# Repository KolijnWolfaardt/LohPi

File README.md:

# LohPi
A Lora Hat for Raspberry Pi

The PCB uses a [Semtech SX1301](http://www.semtech.com/images/datasheet/sx1301.pdf) to implement a full gateway for a LoRaWan connection. It is intended to plug into a Raspberri Pi 3 which manages the packet forwarding. 

# RF Frontend
The RF frontend is responsible for mixing down the signal, sampling it as IQ samples, and sending it to the SX1301 IC. For this two [SX1257](http://www.semtech.com/images/datasheet/sx1257.pdf) ICs are used. The schematic of the RF frontend is adapted from [Microchip's Documentation](http://ww1.microchip.com/downloads/en/DeviceDoc/40001827A.pdf).

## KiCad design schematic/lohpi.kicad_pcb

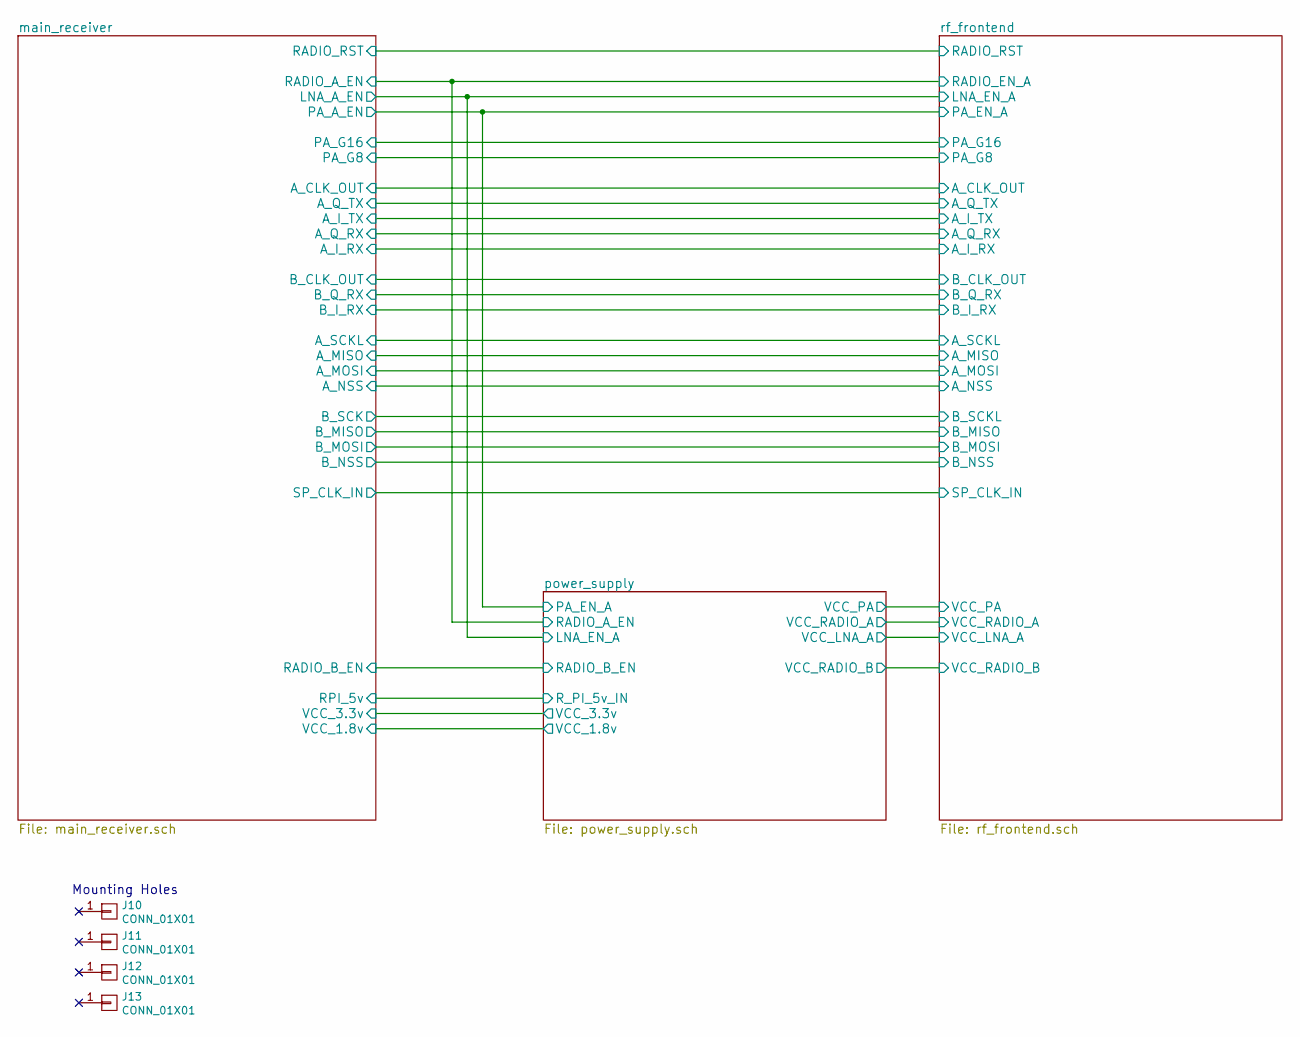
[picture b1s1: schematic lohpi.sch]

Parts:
J10, J11, J12, J13: CONN_01X01; rpi_mounting_hole

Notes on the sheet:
Mounting Holes

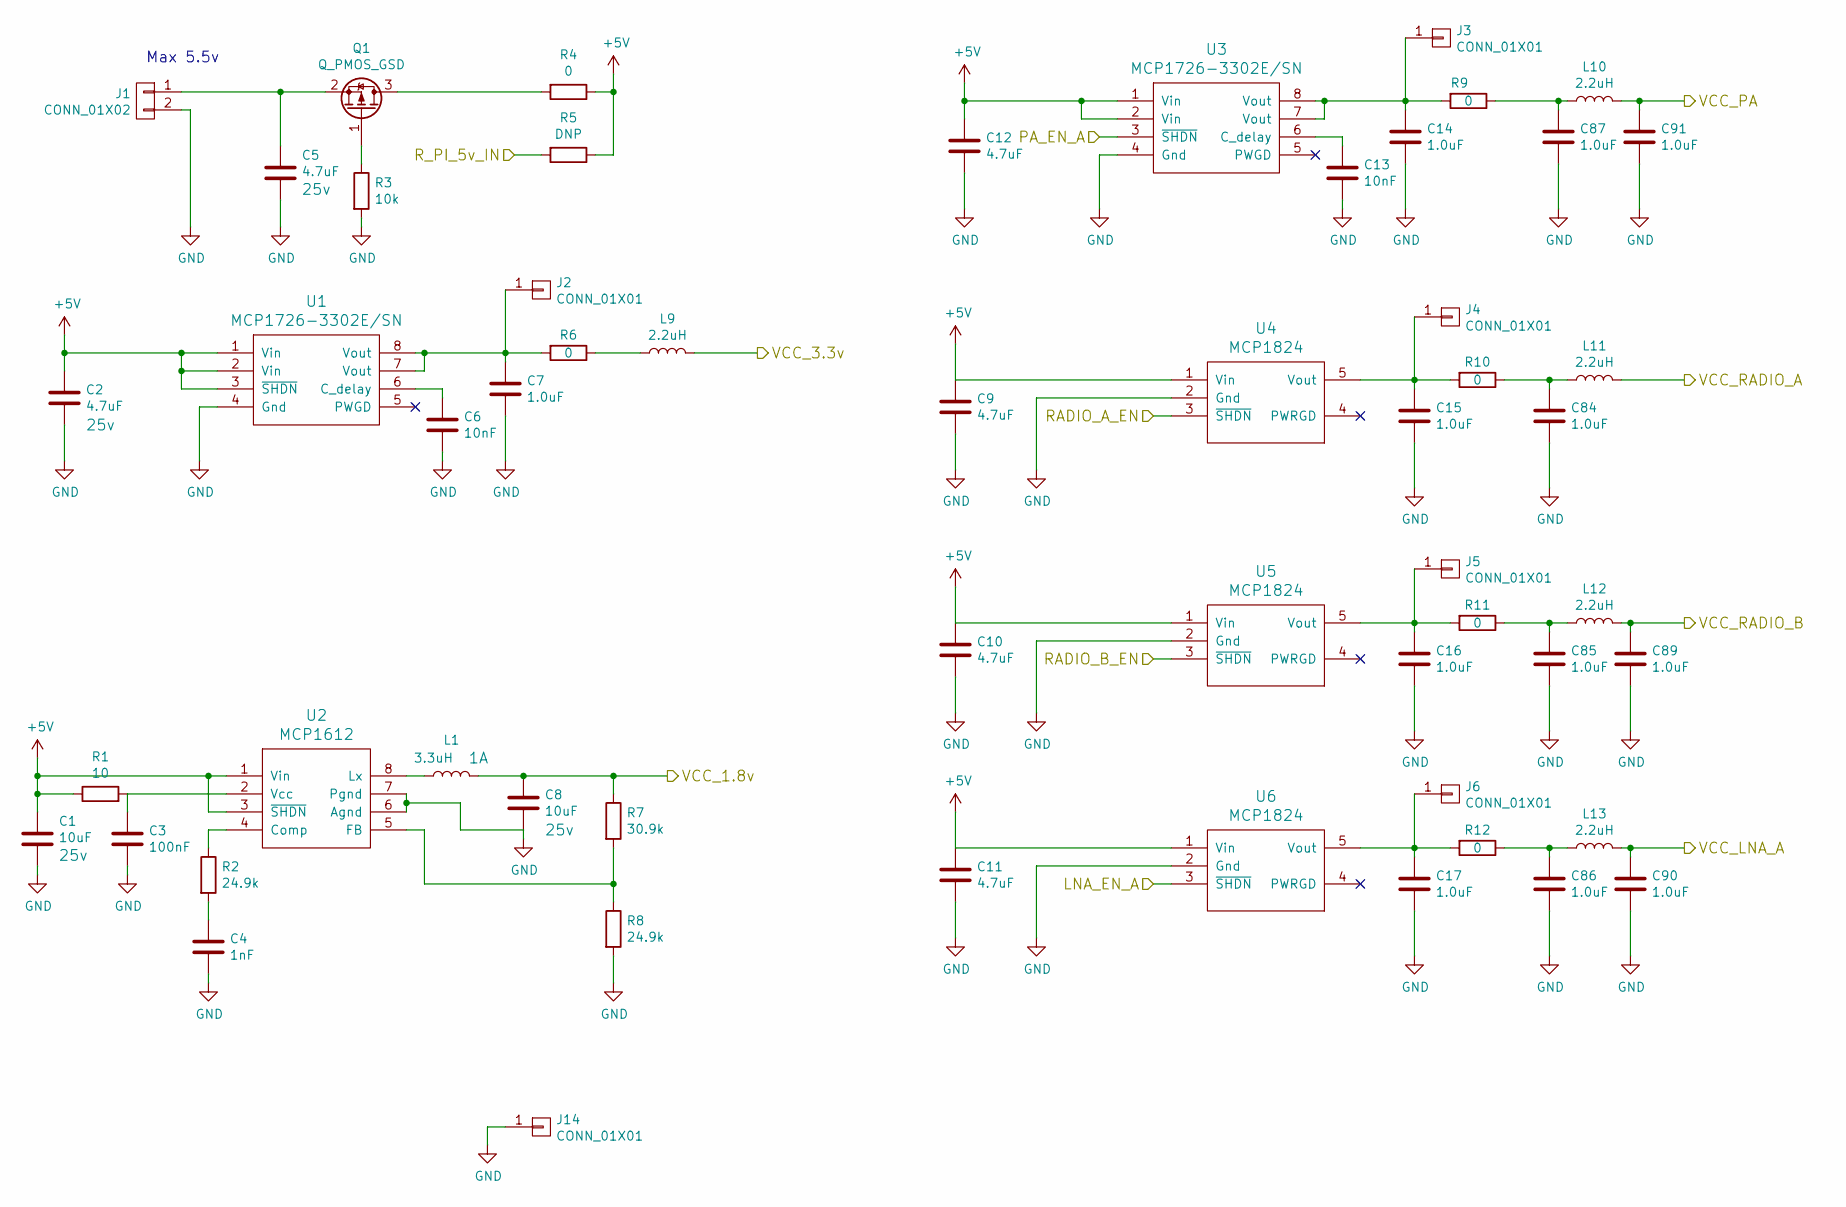
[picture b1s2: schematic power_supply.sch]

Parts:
C1, C8: 10uF; C_0603; Voltage 25v
C2, C5: 4.7uF; C_0603; Voltage 25v
C3: 100nF; C_0603
C4: 1nF; C_0603
C6, C13: 10nF; C_0402_NoSilk
C7, C14, C15, C16, C17, C84, C85, C86, C87, C89, C90, C91: 1.0uF; C_0603
C9, C10, C11, C12: 4.7uF; C_0603
J1: CONN_01X02; Pin_Header_Straight_1x02_Pitch2.54mm
J2, J3, J4, J5, J6, J14: CONN_01X01; Pin_Header_Straight_1x01_Pitch2.54mm
L1: 3.3uH; 84332C
L9, L10, L11, L12, L13: 2.2uH; L_0805
Q1: Q_PMOS_GSD; SOT-23
R1: 10; R_0402_NoSilk
R2, R8: 24.9k; R_0603
R3: 10k; R_0603
R4, R6, R9, R10, R11, R12: 0; R_0603
R5: DNP; R_0603
R7: 30.9k; R_0603
U1, U3: MCP1726-3302E/SN; SOIC-8_3.9x4.9mm_Pitch1.27mm
U2: MCP1612; MSOP-8_3x3mm_Pitch0.65mm
U4, U5, U6: MCP1824; SOT-23-5

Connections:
+1V8: C8.1, L1.2, R7.1; also elsewhere on the board
+3V3: L9.2; also elsewhere on the board
+5V: C1.1, C2.1, C9.1, C10.1, C11.1, C12.1, R1.1, R4.1, R5.1, U1.1 (Vin), U1.2 (Vin), U1.3 (~SHDN), U2.1 (Vin), U2.3 (~SHDN), U3.1 (Vin), U3.2 (Vin), U4.1 (Vin), U5.1 (Vin), U6.1 (Vin)
/main_receiver/LNA_A_EN: U6.3 (~SHDN); also elsewhere on the board
/main_receiver/PA_A_EN: U3.3 (~SHDN); also elsewhere on the board
/main_receiver/RADIO_A_EN: U4.3 (~SHDN); also elsewhere on the board
/main_receiver/RADIO_B_EN: U5.3 (~SHDN); also elsewhere on the board
/main_receiver/RPI_5v: R5.2; also elsewhere on the board
/power_supply/VCC_LNA_A: C90.1, L13.2; also elsewhere on the board
/power_supply/VCC_PA: C91.1, L10.2; also elsewhere on the board
/power_supply/VCC_RADIO_A: L11.2; also elsewhere on the board
/power_supply/VCC_RADIO_B: C89.1, L12.2; also elsewhere on the board
GND: C1.2, C2.2, C3.2, C4.2, C5.2, C6.2, C7.2, C8.2, C9.2, C10.2, C11.2, C12.2, C13.2, C14.2, C15.2, C16.2, C17.2, C84.2, C85.2, C86.2, C87.2, C89.2, C90.2, C91.2, J1.2, J14.1, R3.2, R8.2, U1.4 (Gnd), U2.6 (Agnd), U2.7 (Pgnd), U3.4 (Gnd), U4.2 (Gnd), U5.2 (Gnd), U6.2 (Gnd); also elsewhere on the board
unnamed: C3.1, R1.2, U2.2 (Vcc)
unnamed: C4.1, R2.2
unnamed: C5.1, J1.1, Q1.2 (S)
unnamed: C6.1, U1.6 (C_delay)
unnamed: C7.1, J2.1, R6.2, U1.7 (Vout), U1.8 (Vout)
unnamed: C13.1, U3.6 (C_delay)
unnamed: C14.1, J3.1, R9.2, U3.7 (Vout), U3.8 (Vout)
unnamed: C15.1, J4.1, R10.2, U4.5 (Vout)
unnamed: C16.1, J5.1, R11.2, U5.5 (Vout)
unnamed: C17.1, J6.1, R12.2, U6.5 (Vout)
unnamed: C84.1, L11.1, R10.1
unnamed: C85.1, L12.1, R11.1
unnamed: C86.1, L13.1, R12.1
unnamed: C87.1, L10.1, R9.1
unnamed: L1.1, U2.8 (Lx)
unnamed: L9.1, R6.1
unnamed: Q1.1 (G), R3.1
unnamed: Q1.3 (D), R4.2
unnamed: R2.1, U2.4 (Comp)
unnamed: R7.2, R8.1, U2.5 (FB)

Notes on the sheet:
Max 5.5v

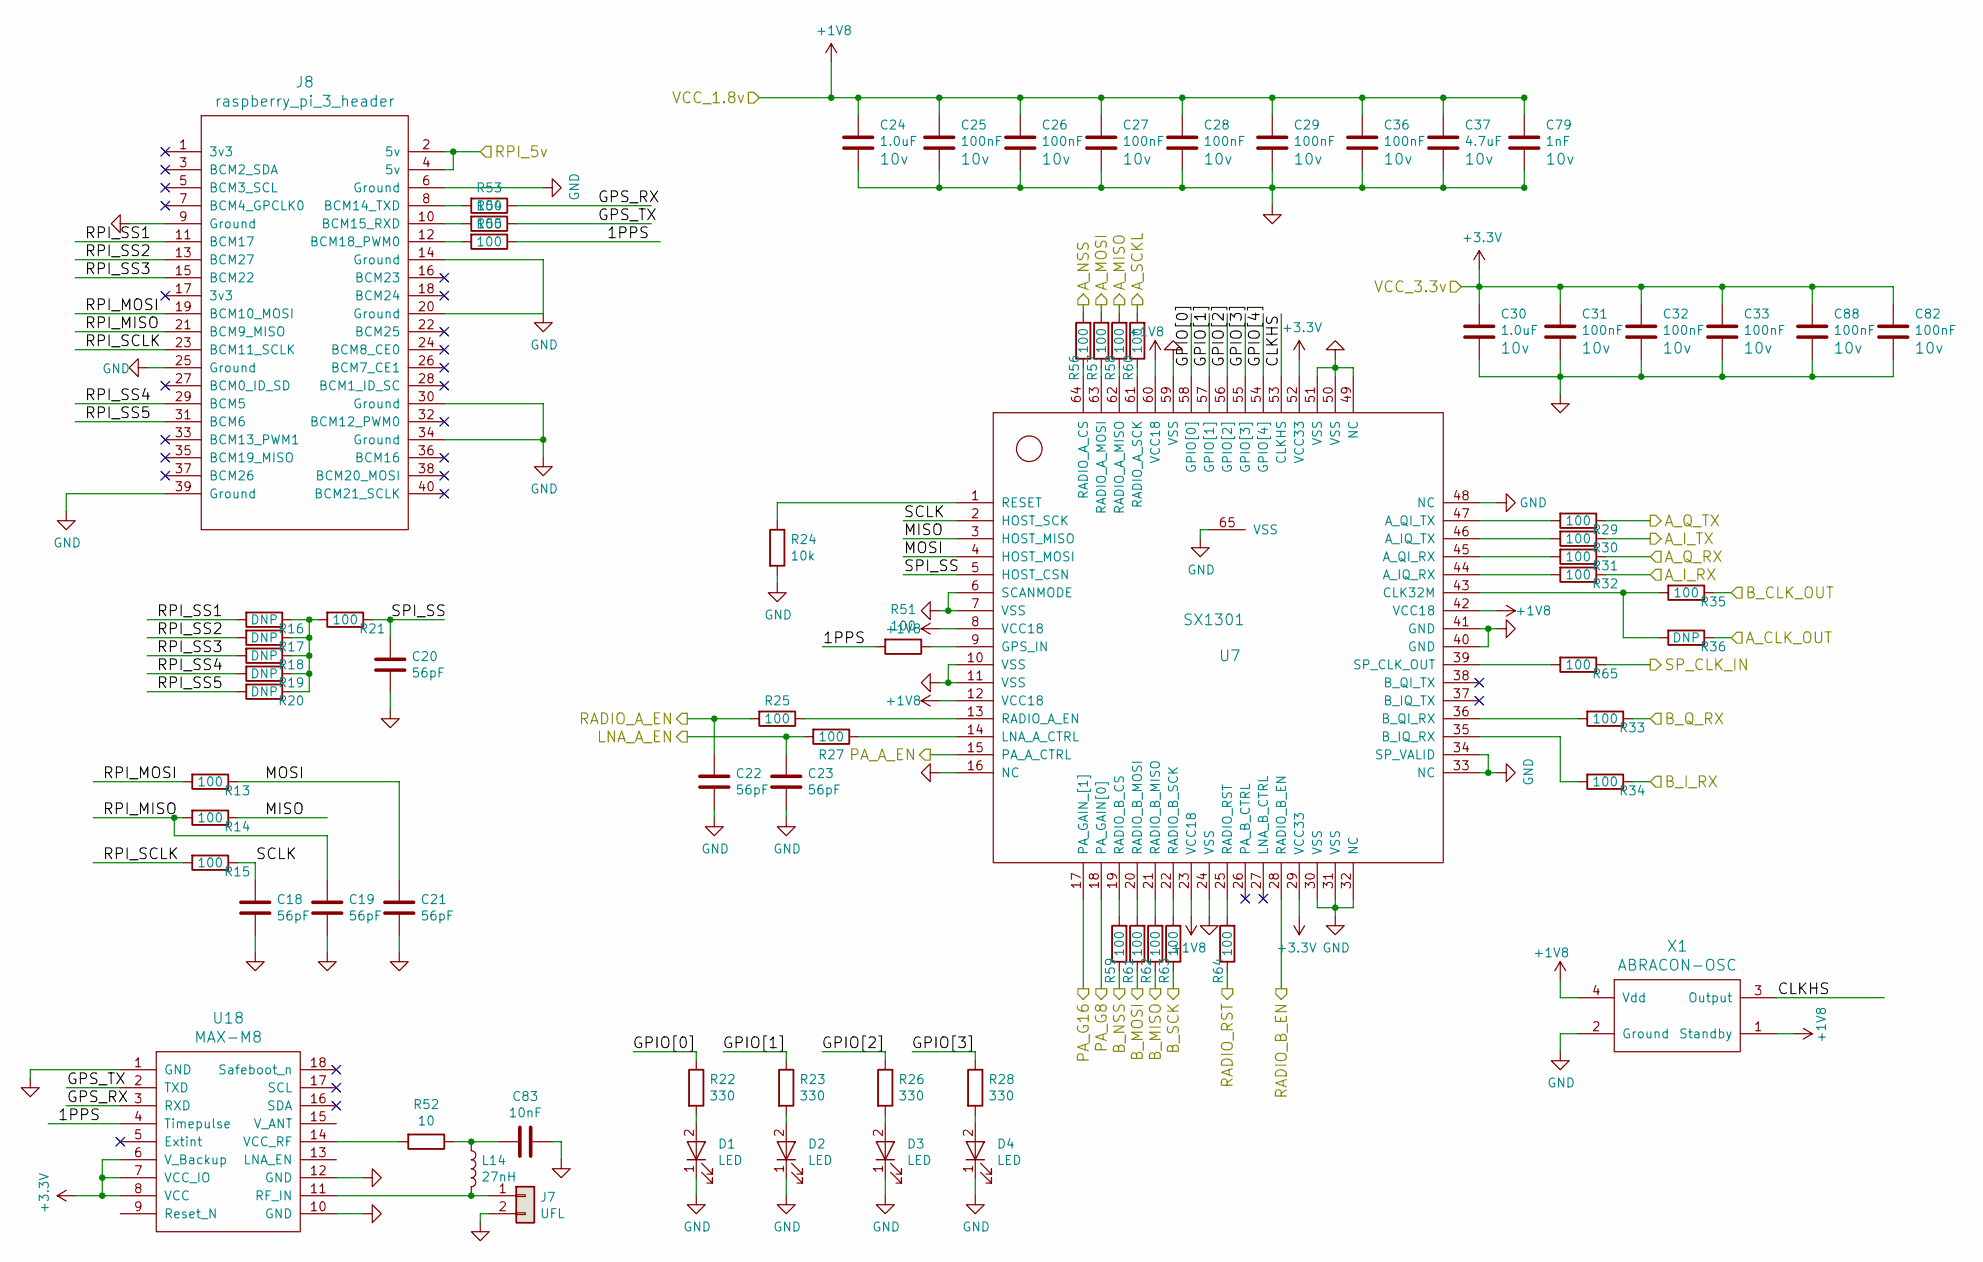
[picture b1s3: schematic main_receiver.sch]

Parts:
C18, C19, C20, C21, C22, C23: 56pF; C_0402_NoSilk
C24, C30: 1.0uF; C_0603; Voltage 10v
C25, C26, C27, C28, C29, C31, C32, C33: 100nF; C_0603; Voltage 10v
C36, C82, C88: 100nF; C_0402_NoSilk; Voltage 10v
C37: 4.7uF; C_0603; Voltage 10v
C79: 1nF; C_0603; Voltage 10v
C83: 10nF; C_0402_NoSilk
D1, D2, D3, D4: LED; LED_0603
J7: UFL; u.fl
J8: raspberry_pi_3_header; Socket_Strip_Straight_2x20_Pitch2.54mm
L14: 27nH; L_0402
R13, R14, R15, R21, R25, R27, R29, R30, R31, R32, R33, R34, R35, R51, R53, R54, R55: 100; R_0603
R16, R17, R18, R19, R20, R36: DNP; R_0603
R22, R23, R26, R28: 330; R_0603
R24: 10k; R_0603
R52: 10; R_0402_NoSilk
R56, R57, R58, R59, R60, R61, R62, R63, R64, R65: 100; R_0402_NoSilk
U7: SX1301; QFN-64-1EP_9x9mm_Pitch0.5mm
U18: MAX-M8
X1: ABRACON-OSC

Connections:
+1V8: C24.1, C25.1, C26.1, C27.1, C28.1, C29.1, C36.1, C37.1, C79.1, U7.8 (VCC18), U7.12 (VCC18), U7.23 (VCC18), U7.42 (VCC18), U7.60 (VCC18), X1.1 (Standby), X1.4 (Vdd); also elsewhere on the board
+3V3: C30.1, C31.1, C32.1, C33.1, C82.1, C88.1, U7.29 (VCC33), U7.52 (VCC33), U18.6 (V_Backup), U18.7 (VCC_IO), U18.8 (VCC); also elsewhere on the board
/main_receiver/1PPS: R51.2, R55.1, U18.4 (Timepulse)
/main_receiver/A_CLK_OUT: R36.1; also elsewhere on the board
/main_receiver/A_I_RX: R32.1; also elsewhere on the board
/main_receiver/A_I_TX: R30.1; also elsewhere on the board
/main_receiver/A_MISO: R58.2; also elsewhere on the board
/main_receiver/A_MOSI: R57.2; also elsewhere on the board
/main_receiver/A_NSS: R56.2; also elsewhere on the board
/main_receiver/A_Q_RX: R31.1; also elsewhere on the board
/main_receiver/A_Q_TX: R29.1; also elsewhere on the board
/main_receiver/A_SCKL: R60.2; also elsewhere on the board
/main_receiver/B_CLK_OUT: R35.1; also elsewhere on the board
/main_receiver/B_I_RX: R34.1; also elsewhere on the board
/main_receiver/B_MISO: R62.1; also elsewhere on the board
/main_receiver/B_MOSI: R61.1; also elsewhere on the board
/main_receiver/B_NSS: R59.1; also elsewhere on the board
/main_receiver/B_Q_RX: R33.1; also elsewhere on the board
/main_receiver/B_SCK: R63.1; also elsewhere on the board
/main_receiver/CLKHS: U7.53 (CLKHS), X1.3 (Output)
/main_receiver/GPIO[0]: R22.1, U7.58 (GPIO[0])
/main_receiver/GPIO[1]: R23.1, U7.57 (GPIO[1])
/main_receiver/GPIO[2]: R26.1, U7.56 (GPIO[2])
/main_receiver/GPIO[3]: R28.1, U7.55 (GPIO[3])
/main_receiver/GPS_RX: R53.1, U18.3 (RXD)
/main_receiver/GPS_TX: R54.1, U18.2 (TXD)
/main_receiver/LNA_A_EN: C23.1, R27.2; also elsewhere on the board
/main_receiver/MISO: R14.1, U7.3 (HOST_MISO)
/main_receiver/MOSI: C21.1, R13.1, U7.4 (HOST_MOSI)
/main_receiver/PA_A_EN: U7.15 (PA_A_CTRL); also elsewhere on the board
/main_receiver/PA_G8: U7.18 (PA_GAIN[0]); also elsewhere on the board
/main_receiver/PA_G16: U7.17 (PA_GAIN_[1]); also elsewhere on the board
/main_receiver/RADIO_A_EN: C22.1, R25.2; also elsewhere on the board
/main_receiver/RADIO_B_EN: U7.28 (RADIO_B_EN); also elsewhere on the board
/main_receiver/RADIO_RST: R64.1; also elsewhere on the board
/main_receiver/RPI_5v: J8.2 (5v), J8.4 (5v); also elsewhere on the board
/main_receiver/RPI_MISO: C19.1, J8.21 (BCM9_MISO), R14.2
/main_receiver/RPI_MOSI: J8.19 (BCM10_MOSI), R13.2
/main_receiver/RPI_SCLK: J8.23 (BCM11_SCLK), R15.2
/main_receiver/RPI_SS1: J8.11 (BCM17), R16.2
/main_receiver/RPI_SS2: J8.13 (BCM27), R17.2
/main_receiver/RPI_SS3: J8.15 (BCM22), R18.2
/main_receiver/RPI_SS4: J8.29 (BCM5), R19.2
/main_receiver/RPI_SS5: J8.31 (BCM6), R20.2
/main_receiver/SCLK: C18.1, R15.1, U7.2 (HOST_SCK)
/main_receiver/SPI_SS: C20.1, R21.1, U7.5 (HOST_CSN)
/main_receiver/SP_CLK_IN: R65.1; also elsewhere on the board
GND: C18.2, C19.2, C20.2, C21.2, C22.2, C23.2, C24.2, C25.2, C26.2, C27.2, C28.2, C29.2, C30.2, C31.2, C32.2, C33.2, C36.2, C37.2, C79.2, C82.2, C83.1, C88.2, D1.1 (K), D2.1 (K), D3.1 (K), D4.1 (K), J7.2, J8.6 (Ground), J8.9 (Ground), J8.14 (Ground), J8.20 (Ground), J8.25 (Ground), J8.30 (Ground), J8.34 (Ground), J8.39 (Ground), R24.2, U7.6 (SCANMODE), U7.7 (VSS), U7.10 (VSS), U7.11 (VSS), U7.16 (NC), U7.24 (VSS), U7.30 (VSS), U7.31 (VSS), U7.32 (NC), U7.33 (NC), U7.34 (SP_VALID), U7.40 (GND), U7.41 (GND), U7.48 (NC), U7.49 (NC), U7.50 (VSS), U7.51 (VSS), U7.59 (VSS), U7.65 (VSS), U18.1 (GND), U18.10 (GND), U18.12 (GND), X1.2 (Ground); also elsewhere on the board
unnamed: C83.2, L14.1, R52.1
unnamed: D1.2 (A), R22.2
unnamed: D2.2 (A), R23.2
unnamed: D3.2 (A), R26.2
unnamed: D4.2 (A), R28.2
unnamed: J7.1, L14.2, U18.11 (RF_IN)
unnamed: J8.8 (BCM14_TXD), R53.2
unnamed: J8.10 (BCM15_RXD), R54.2
unnamed: J8.12 (BCM18_PWM0), R55.2
unnamed: R16.1, R17.1, R18.1, R19.1, R20.1, R21.2
unnamed: R24.1, U7.1 (RESET)
unnamed: R25.1, U7.13 (RADIO_A_EN)
unnamed: R27.1, U7.14 (LNA_A_CTRL)
unnamed: R29.2, U7.47 (A_QI_TX)
unnamed: R30.2, U7.46 (A_IQ_TX)
unnamed: R31.2, U7.45 (A_QI_RX)
unnamed: R32.2, U7.44 (A_IQ_RX)
unnamed: R33.2, U7.36 (B_QI_RX)
unnamed: R34.2, U7.35 (B_IQ_RX)
unnamed: R35.2, R36.2, U7.43 (CLK32M)
unnamed: R51.1, U7.9 (GPS_IN)
unnamed: R52.2, U18.14 (VCC_RF)
unnamed: R56.1, U7.64 (RADIO_A_CS)
unnamed: R57.1, U7.63 (RADIO_A_MOSI)
unnamed: R58.1, U7.62 (RADIO_A_MISO)
unnamed: R59.2, U7.19 (RADIO_B_CS)
unnamed: R60.1, U7.61 (RADIO_A_SCK)
unnamed: R61.2, U7.20 (RADIO_B_MOSI)
unnamed: R62.2, U7.21 (RADIO_B_MISO)
unnamed: R63.2, U7.22 (RADIO_B_SCK)
unnamed: R64.2, U7.25 (RADIO_RST)
unnamed: R65.2, U7.39 (SP_CLK_OUT)

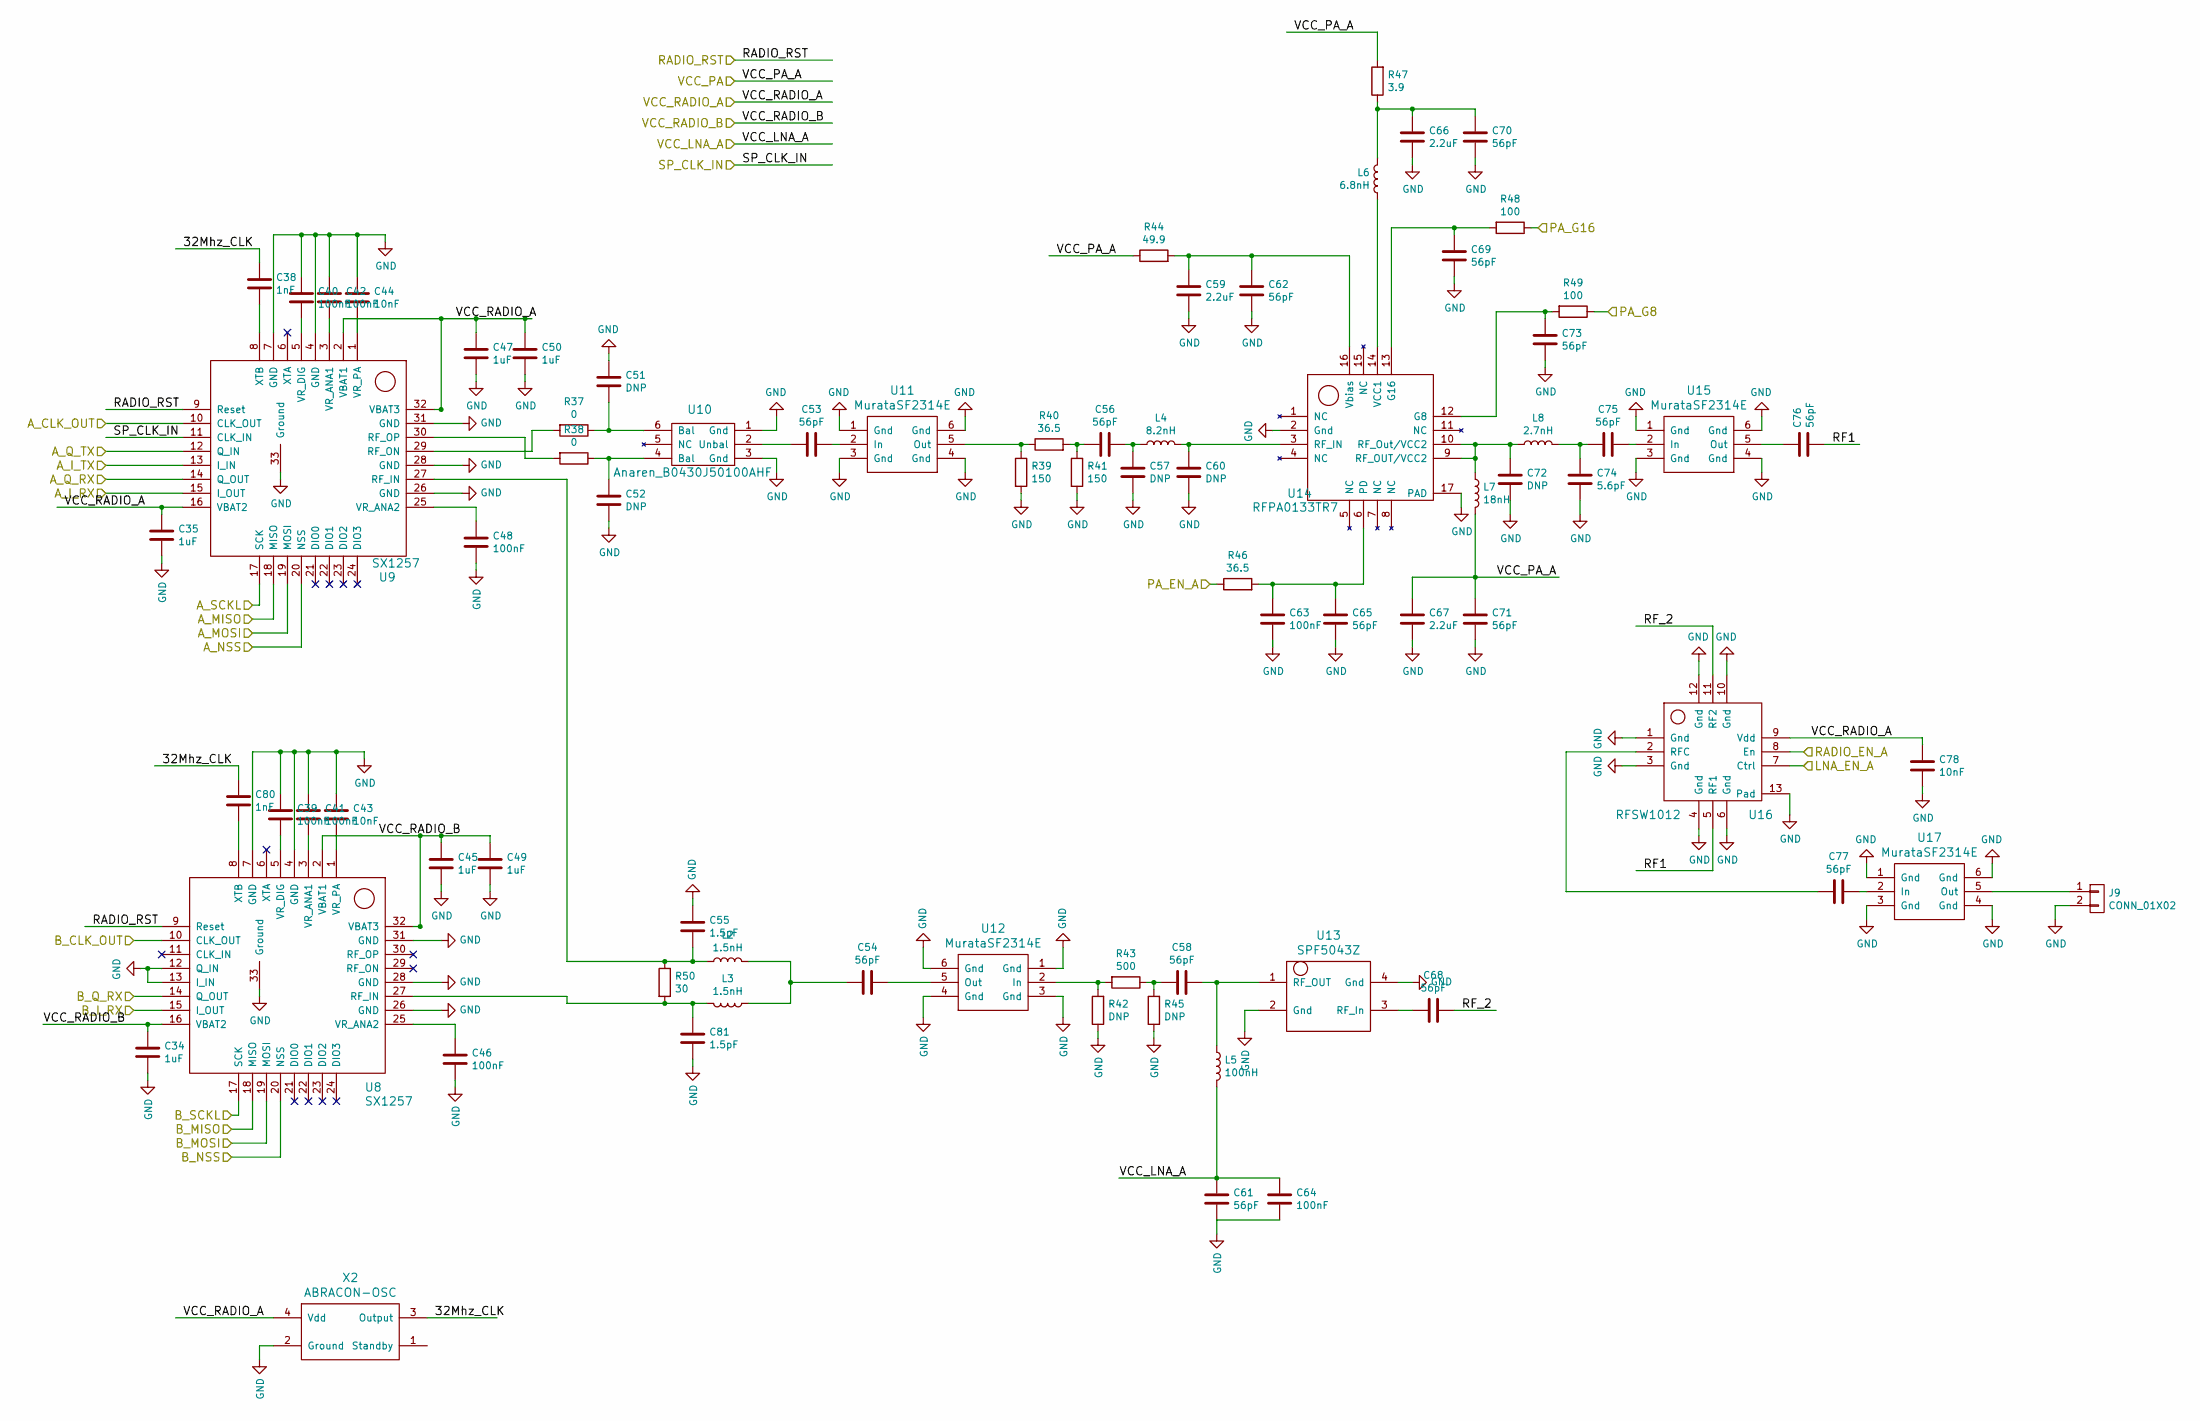
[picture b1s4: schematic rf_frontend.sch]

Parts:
C34, C35, C45, C47, C49, C50: 1uF; C_0402_NoSilk
C38, C80: 1nF; C_0603
C39, C40, C41, C42, C46, C48, C63, C64: 100nF; C_0402_NoSilk
C43, C44, C78: 10nF; C_0402_NoSilk
C51, C52, C57, C60, C72: DNP; C_0402_NoSilk
C53, C54, C56, C58, C61, C62, C65, C68, C69, C70, C71, C73, C75, C76, C77: 56pF; C_0402_NoSilk
C55, C81: 1.5pF; C_0402_NoSilk
C59, C66, C67: 2.2uF; C_0402_NoSilk
C74: 5.6pF; C_0402_NoSilk
J9: CONN_01X02; SMA_THT_Jack_Straight
L2, L3: 1.5nH; L_0402
L4: 8.2nH; L_0402
L5: 100nH; L_0402
L6: 6.8nH; L_0402
L7: 18nH; L_0402
L8: 2.7nH; L_0402
R37, R38: 0; R_0402_NoSilk
R39, R41: 150; R_0402_NoSilk
R40, R46: 36.5; R_0402_NoSilk
R42, R45: DNP; R_0402_NoSilk
R43: 500; R_0402_NoSilk
R44: 49.9; R_0402_NoSilk
R47: 3.9; R_0402_NoSilk
R48, R49: 100; R_0402_NoSilk
R50: 30; R_0402_NoSilk
U8, U9: SX1257; QFN-32-1EP_5x5mm_Pitch0.5mm
U10: Anaren_B0430J50100AHF; anaren_balun
U11, U12, U15, U17: MurataSF2314E; murata_saw_filter
U13: SPF5043Z; quorvo_spf5043z
U14: RFPA0133TR7; QFN-16-1EP_3x3mm_Pitch0.5mm
U16: RFSW1012; rfsw1012DS
X2: ABRACON-OSC

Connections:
/main_receiver/A_CLK_OUT: U9.10 (CLK_OUT); also elsewhere on the board
/main_receiver/A_I_RX: U9.15 (I_OUT); also elsewhere on the board
/main_receiver/A_I_TX: U9.13 (I_IN); also elsewhere on the board
/main_receiver/A_MISO: U9.18 (MISO); also elsewhere on the board
/main_receiver/A_MOSI: U9.19 (MOSI); also elsewhere on the board
/main_receiver/A_NSS: U9.20 (NSS); also elsewhere on the board
/main_receiver/A_Q_RX: U9.14 (Q_OUT); also elsewhere on the board
/main_receiver/A_Q_TX: U9.12 (Q_IN); also elsewhere on the board
/main_receiver/A_SCKL: U9.17 (SCK); also elsewhere on the board
/main_receiver/B_CLK_OUT: U8.10 (CLK_OUT); also elsewhere on the board
/main_receiver/B_I_RX: U8.15 (I_OUT); also elsewhere on the board
/main_receiver/B_MISO: U8.18 (MISO); also elsewhere on the board
/main_receiver/B_MOSI: U8.19 (MOSI); also elsewhere on the board
/main_receiver/B_NSS: U8.20 (NSS); also elsewhere on the board
/main_receiver/B_Q_RX: U8.14 (Q_OUT); also elsewhere on the board
/main_receiver/B_SCK: U8.17 (SCK); also elsewhere on the board
/main_receiver/LNA_A_EN: U16.7 (Ctrl); also elsewhere on the board
/main_receiver/PA_A_EN: R46.1; also elsewhere on the board
/main_receiver/PA_G8: R49.1; also elsewhere on the board
/main_receiver/PA_G16: R48.1; also elsewhere on the board
/main_receiver/RADIO_A_EN: U16.8 (En); also elsewhere on the board
/main_receiver/RADIO_RST: U8.9 (Reset), U9.9 (Reset); also elsewhere on the board
/main_receiver/SP_CLK_IN: U9.11 (CLK_IN); also elsewhere on the board
/power_supply/VCC_LNA_A: C61.2, C64.2, L5.2; also elsewhere on the board
/power_supply/VCC_PA: C67.2, C71.2, L7.2, R44.1, R47.2; also elsewhere on the board
/power_supply/VCC_RADIO_A: C35.1, C47.1, C50.1, C78.2, U9.2 (VBAT1), U9.16 (VBAT2), U9.32 (VBAT3), U16.9 (Vdd), X2.4 (Vdd); also elsewhere on the board
/power_supply/VCC_RADIO_B: C34.1, C45.1, C49.1, U8.2 (VBAT1), U8.16 (VBAT2), U8.32 (VBAT3); also elsewhere on the board
/rf_frontend/32Mhz_CLK: C38.1, C80.1, X2.3 (Output)
/rf_frontend/RF1: C76.2, U16.5 (RF1)
/rf_frontend/RF_2: C68.1, U16.11 (RF2)
GND: C34.2, C35.2, C39.1, C40.1, C41.1, C42.1, C43.1, C44.1, C45.2, C46.2, C47.2, C48.2, C49.2, C50.2, C51.2, C52.1, C55.1, C57.2, C59.2, C60.2, C61.1, C62.2, C63.2, C64.1, C65.2, C66.1, C67.1, C69.1, C70.1, C71.1, C72.2, C73.1, C74.2, C78.1, C81.2, J9.2, R39.2, R41.2, R42.1, R45.1, U8.4 (GND), U8.7 (GND), U8.12 (Q_IN), U8.13 (I_IN), U8.26 (GND), U8.28 (GND), U8.31 (GND), U8.33 (Ground), U9.4 (GND), U9.7 (GND), U9.26 (GND), U9.28 (GND), U9.31 (GND), U9.33 (Ground), U10.1 (Gnd), U10.3 (Gnd), U11.1 (Gnd), U11.3 (Gnd), U11.4 (Gnd), U11.6 (Gnd), U12.1 (Gnd), U12.3 (Gnd), U12.4 (Gnd), U12.6 (Gnd), U13.2 (Gnd), U13.4 (Gnd), U14.2 (Gnd), U14.17 (PAD), U15.1 (Gnd), U15.3 (Gnd), U15.4 (Gnd), U15.6 (Gnd), U16.1 (Gnd), U16.3 (Gnd), U16.4 (Gnd), U16.6 (Gnd), U16.10 (Gnd), U16.12 (Gnd), U16.13 (Pad), U17.1 (Gnd), U17.3 (Gnd), U17.4 (Gnd), U17.6 (Gnd), X2.2 (Ground); also elsewhere on the board
unnamed: C38.2, U9.8 (XTB)
unnamed: C39.2, U8.5 (VR_DIG)
unnamed: C40.2, U9.5 (VR_DIG)
unnamed: C41.2, U8.3 (VR_ANA1)
unnamed: C42.2, U9.3 (VR_ANA1)
unnamed: C43.2, U8.1 (VR_PA)
unnamed: C44.2, U9.1 (VR_PA)
unnamed: C46.1, U8.25 (VR_ANA2)
unnamed: C48.1, U9.25 (VR_ANA2)
unnamed: C51.1, R37.1, U10.6 (Bal)
unnamed: C52.2, R38.1, U10.4 (Bal)
unnamed: C53.1, U10.2 (Unbal)
unnamed: C53.2, U11.2 (In)
unnamed: C54.1, U12.5 (Out)
unnamed: C54.2, L2.2, L3.1
unnamed: C55.2, L2.1, R50.1, U9.27 (RF_IN)
unnamed: C56.1, R40.2, R41.1
unnamed: C56.2, C57.1, L4.1
unnamed: C58.1, L5.1, U13.1 (RF_OUT)
unnamed: C58.2, R43.1, R45.2
unnamed: C59.1, C62.1, R44.2, U14.16 (Vbias)
unnamed: C60.1, L4.2, U14.3 (RF_IN)
unnamed: C63.1, C65.1, R46.2, U14.6 (PD)
unnamed: C66.2, C70.2, L6.1, R47.1
unnamed: C68.2, U13.3 (RF_In)
unnamed: C69.2, R48.2, U14.13 (G16)
unnamed: C72.1, L7.1, L8.1, U14.9 (RF_OUT/VCC2), U14.10 (RF_Out/VCC2)
unnamed: C73.2, R49.2, U14.12 (G8)
unnamed: C74.1, C75.2, L8.2
unnamed: C75.1, U15.2 (In)
unnamed: C76.1, U15.5 (Out)
unnamed: C77.1, U17.2 (In)
unnamed: C77.2, U16.2 (RFC)
unnamed: C80.2, U8.8 (XTB)
unnamed: C81.1, L3.2, R50.2, U8.27 (RF_IN)
unnamed: J9.1, U17.5 (Out)
unnamed: L6.2, U14.14 (VCC1)
unnamed: R37.2, U9.29 (RF_ON)
unnamed: R38.2, U9.30 (RF_OP)
unnamed: R39.1, R40.1, U11.5 (Out)
unnamed: R42.2, R43.2, U12.2 (In)

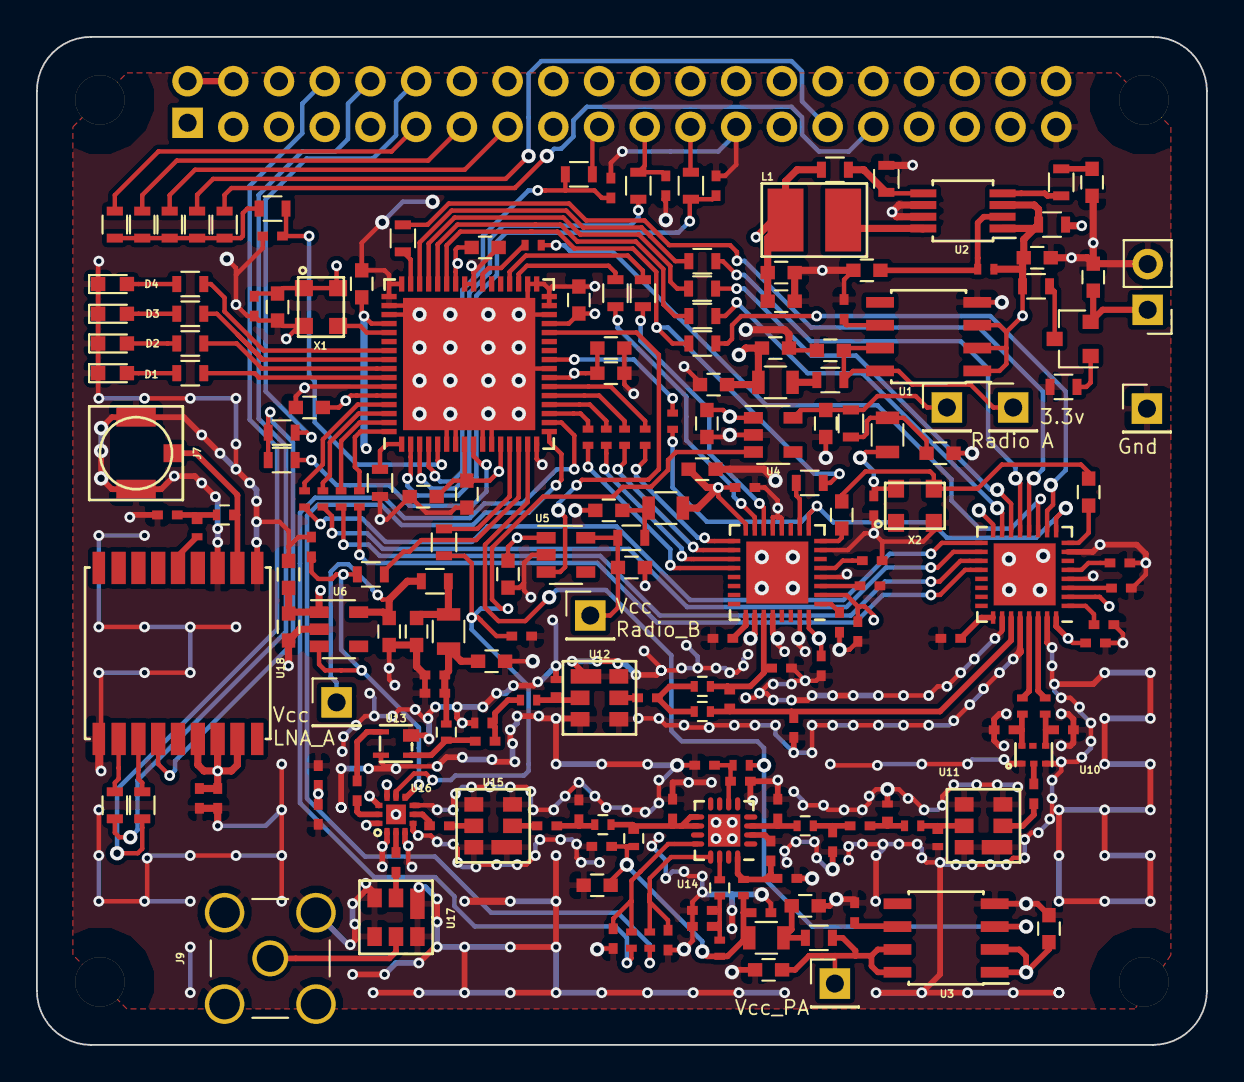
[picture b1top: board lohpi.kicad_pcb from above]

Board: 4 copper layers, 65.0 x 56.0 mm, 209 parts (1 on the bottom side), 149 nets.

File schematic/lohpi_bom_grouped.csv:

Reference, Quantity, Value, Footprint, Datasheet, Voltage, I
C1 C8 ,2,"10uF","Capacitors_SMD:C_0603","","25v",""
C10 C11 C12 C2 C37 C5 C9 ,7,"4.7uF","Capacitors_SMD:C_0603",""
C13 C43 C44 C6 C78 C83 ,6,"10nF","Capacitors_SMD:C_0402_NoSilk",""
C14 C15 C16 C17 C24 C30 C7 C84 C85 C86 C87 C89 C90 C91 ,14,"1.0uF","Capacitors_SMD:C_0603",""
C18 C19 C20 C21 C22 C23 C53 C54 C56 C58 C61 C62 C65 C68 C69 C70 C71 C73 C75 C76 C77 ,21,"56pF","Capacitors_SMD:C_0402_NoSilk",""
C25 C26 C27 C28 C29 C3 C31 C32 C33 ,9,"100nF","Capacitors_SMD:C_0603",""
C34 C35 C45 C47 C49 C50 ,6,"1uF","Capacitors_SMD:C_0402_NoSilk",""
C36 C39 C40 C41 C42 C46 C48 C63 C64 C82 C88 ,11,"100nF","Capacitors_SMD:C_0402_NoSilk","","10v",""
C38 C4 C79 C80 ,4,"1nF","Capacitors_SMD:C_0603",""
C51 C52 C57 C60 C72 ,5,"DNP","Capacitors_SMD:C_0402_NoSilk",""
C55 C81 ,2,"1.5pF","Capacitors_SMD:C_0402_NoSilk",""
C59 C66 C67 ,3,"2.2uF","Capacitors_SMD:C_0402_NoSilk",""
C74 ,1,"5.6pF","Capacitors_SMD:C_0402_NoSilk",""
D1 D2 D3 D4 ,4,"LED","LEDs:LED_0603",""
J1 ,1,"CONN_01X02","Pin_Headers:Pin_Header_Straight_1x02_Pitch2.54mm",""
J10 J11 J12 J13 ,4,"CONN_01X01","rpi_mounting_hole:rpi_mounting_hole",""
J2 J3 J4 J5 J6 ,5,"CONN_01X01","Pin_Headers:Pin_Header_Straight_1x01_Pitch2.54mm",""
J7 ,1,"UFL","hirose:u.fl",""
J8 ,1,"raspberry_pi_3_header","Socket_Strips:Socket_Strip_Straight_2x20_Pitch2.54mm",""
J9 ,1,"CONN_01X02","Connectors:SMA_THT_Jack_Straight",""
L1 ,1,"3.3uH","Inductors_SMD:L_0603","","","1A"
L10 L11 L12 L13 L9 ,5,"2.2uH","Inductors_SMD:L_0805",""
L14 ,1,"27nH","Inductors_SMD:L_0402",""
L2 L3 ,2,"1.5nH","Inductors_SMD:L_0402",""
L4 ,1,"8.2nH","Inductors_SMD:L_0402",""
L5 ,1,"100nH","Inductors_SMD:L_0402",""
L6 ,1,"6.8nH","Inductors_SMD:L_0402",""
L7 ,1,"18nH","Inductors_SMD:L_0402",""
L8 ,1,"2.7nH","Inductors_SMD:L_0402",""
Q1 ,1,"Q_PMOS_GSD","TO_SOT_Packages_SMD:SOT-23",""
R1 R52 ,2,"10","Resistors_SMD:R_0402_NoSilk",""
R2 R8 ,2,"24.9k","Resistors_SMD:R_0603",""
R22 R23 R26 R28 ,4,"330","Resistors_SMD:R_0603",""
R24 R3 ,2,"10k","Resistors_SMD:R_0603",""
R13 R14 R15 R21 R25 R27 R29 R30 R31 R32 R33 R34 R35 R51 R53 R54 R55 ,17,"100","Resistors_SMD:R_0603",""
R37 R38 ,2,"0","Resistors_SMD:R_0402_NoSilk",""
R39 R41 ,2,"150","Resistors_SMD:R_0402_NoSilk",""
R10 R11 R12 R4 R6 R9 ,6,"0","Resistors_SMD:R_0603",""
R40 R46 ,2,"36.5","Resistors_SMD:R_0402_NoSilk",""
R43 ,1,"500","Resistors_SMD:R_0402_NoSilk",""
R44 ,1,"49.9","Resistors_SMD:R_0402_NoSilk",""
R42 R45 ,2,"DNP","Resistors_SMD:R_0402_NoSilk",""
R47 ,1,"3.9","Resistors_SMD:R_0402_NoSilk",""
R48 R49 ,2,"100","Resistors_SMD:R_0402_NoSilk",""
R16 R17 R18 R19 R20 R36 R5 ,7,"DNP","Resistors_SMD:R_0603",""
R50 ,1,"30","Resistors_SMD:R_0402_NoSilk",""
R7 ,1,"30.9k","Resistors_SMD:R_0603",""
U10 ,1,"Anaren_B0430J50100AHF","anaren_balun:anaren_balun",""
U11 U12 U15 U17 ,4,"MurataSF2314E","murata_saw_filter:murata_saw_filter",""
U13 ,1,"SPF5043Z","quorvo:quorvo_spf5043z",""
U14 ,1,"RFPA0133TR7","Housings_DFN_QFN:QFN-16-1EP_3x3mm_Pitch0.5mm",""
U16 ,1,"RFSW1012","quorvo:rfsw1012DS",""
U18 ,1,"MAX-M8","max_8:MAX-M8",""
U2 ,1,"MCP1612","Housings_SSOP:MSOP-8_3x3mm_Pitch0.65mm",""
U1 U3 ,2,"MCP1726-3302E/SN","Housings_SOIC:SOIC-8_3.9x4.9mm_Pitch1.27mm",""
U4 U5 U6 ,3,"MCP1824","TO_SOT_Packages_SMD:SOT-23-5",""
U7 ,1,"SX1301","Housings_DFN_QFN:QFN-64-1EP_9x9mm_Pitch0.5mm",""
U8 U9 ,2,"SX1257","Housings_DFN_QFN:QFN-32-1EP_5x5mm_Pitch0.5mm",""
X1 X2 ,2,"ABRACON-OSC","crystal_osc_1:ABRACON-OSC",""

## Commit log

2017-09-09 Updates gitignore with less files removed
2017-09-09 First schematic commit. No GPS module yet.
2017-09-09 Updates Readme
2017-09-10 Updates to schematic, components
2017-09-10 Adds footprint for crystal
2017-09-10 Update README.md
    Fix typos
2017-09-23 Schematic capture almost done. RF layout started.
2017-09-30 RF layout updated. Rest still needs work
2017-10-01 PCB layout finished, needs review
2017-10-01 Adds via stitching, better ground infill.
2017-10-03 HF layout changed, GPS module added
2017-10-07 Layout approaching final version. BOM updated
2017-10-11 More updates to bom, added resistors to all communication lines
2017-10-18 Add the rest of the passive components to bom
2017-10-20 Correct component for SMPS inductor, changed footprint
2017-10-21 Moved all references to F.Fab, cleaned up silkscreen
2017-11-12 Version sent to fab
2019-08-07 Convert to Kicad 5, fix Front Fab layer
